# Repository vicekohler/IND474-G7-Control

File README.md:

# Control G7 — gamepad USB con pantalla para juegos de PC

**IND474 Desarrollo de Productos Físicos · Universidad Adolfo Ibáñez · Grupo 7**
Fernando Guaita · Guillermo Hidalgo · Vicente Kohler · Eduardo Rojas

Control G7 es un gamepad USB que el PC reconoce sin drivers. Tiene cruceta, A, B, MENU, un joystick analógico y una pantalla de 1,3" que muestra el modo y las confirmaciones. Funciona como **gamepad HID** (juegos de PC en general) o como **teclado** (juegos que solo aceptan teclado).

## Estado (23/11/2026)

| Parte | Estado |
|---|---|
| PCB D4.4 fabricada y soldada | ✅ |
| Firmware v1.2 (gamepad + teclado, pantalla, recalibración) | ✅ probado en gamepad-tester, SuperTux y el dinosaurio de Chrome |
| Carcasa v6 (Fusion 360) | ✅ diseñada · ⏳ sin imprimir |
| Bring-up medido (3V3, 5V, consumo) | ⏳ pendiente — ver [hardware/bring-up](hardware/bring-up/README.md) |
| Probeta de holguras y muestras CMF | ⏳ pendiente |
| Prueba con 5 usuarios | ⏳ pendiente — ver [experiencia](experiencia/README.md) |

Lo pendiente se marca así a propósito: no publicamos resultados que todavía no medimos.

## Cómo usarlo

1. Enchufar por USB-C **con el stick suelto** (se calibra el centro al conectar).
2. Windows lo muestra como **"Control G7"**.
3. Atajos:
   - **MENU + B (1,5 s):** cambia entre GAMEPAD y TECLADO (queda guardado).
   - **MENU + A (1,5 s):** recalibra el centro del stick.

| Control | Modo GAMEPAD | Modo TECLADO |
|---|---|---|
| Stick | Ejes X / Y | Flechas |
| Cruceta | Hat (con diagonales) | Flechas |
| A / B | Botón 1 / 2 | Z / X |
| MENU | Botón 8 (Start) | Enter |
| Clic del stick | Botón 9 (L3) | Espacio |

## Estructura del repositorio

| Carpeta | Contenido |
|---|---|
| [`hardware/`](hardware) | KiCad, Gerber, BOM, planos, DRC/ERC, cambios desde la D4.4 y bring-up |
| [`firmware/`](firmware) | Firmware `G7_Gamepad` v1.2 y las 4 pruebas por partes con sus lecturas |
| [`cad/`](cad) | Fusion 360 (`.f3d`), STEP del ensamble, STL para imprimir, renders, scripts y modelos de componentes |
| [`experiencia/`](experiencia) | Perfil de usuario, protocolo de la prueba con 5 personas, planilla y resultados |
| [`docs/`](docs) | Presentación (PDF), resumen de la carcasa y diagramas |
| [`DECISIONES.md`](DECISIONES.md) | Decisiones de diseño y por qué cambiaron desde la propuesta |

## Arquitectura

```
Cruceta, A, B, MENU ──┐
Joystick KY-023 ──────┼──► Waveshare RP2350-Plus ──► USB-C ──► PC (gamepad HID o teclado)
                      │     núcleo 0: entradas + USB a 1 kHz
                      │     núcleo 1: pantalla ST7789
```

- **Microcontrolador:** Waveshare RP2350-Plus, soldado por la cara trasera de la PCB.
- **Firmware:** Arduino-Pico 6.3.2 (Arduino IDE 2.3.11) + librerías Adafruit ST7789 y GFX.
- **Carcasa:** concha impresa en PLA/PETG (Bambu A1), pared de 2,4 mm; la PCB se atornilla a la tapa con 4 × M2 y la base cierra con 6 clips.

## Referencias

- [Alpakka — Input Labs](https://inputlabs.io/alpakka): referente de mando abierto (integración física y documentación).
- [Arduino-Pico](https://github.com/earlephilhower/arduino-pico): núcleo sobre el que corre el firmware.
- [Adafruit ST7735/ST7789](https://github.com/adafruit/Adafruit-ST7735-Library) y [Adafruit GFX](https://github.com/adafruit/Adafruit-GFX-Library).
- [Waveshare RP2350-Plus](https://www.waveshare.com/wiki/RP2350-Plus).
- Norman, Rams, Ulrich y Thompson (material del curso) para ergonomía, forma y CMF.

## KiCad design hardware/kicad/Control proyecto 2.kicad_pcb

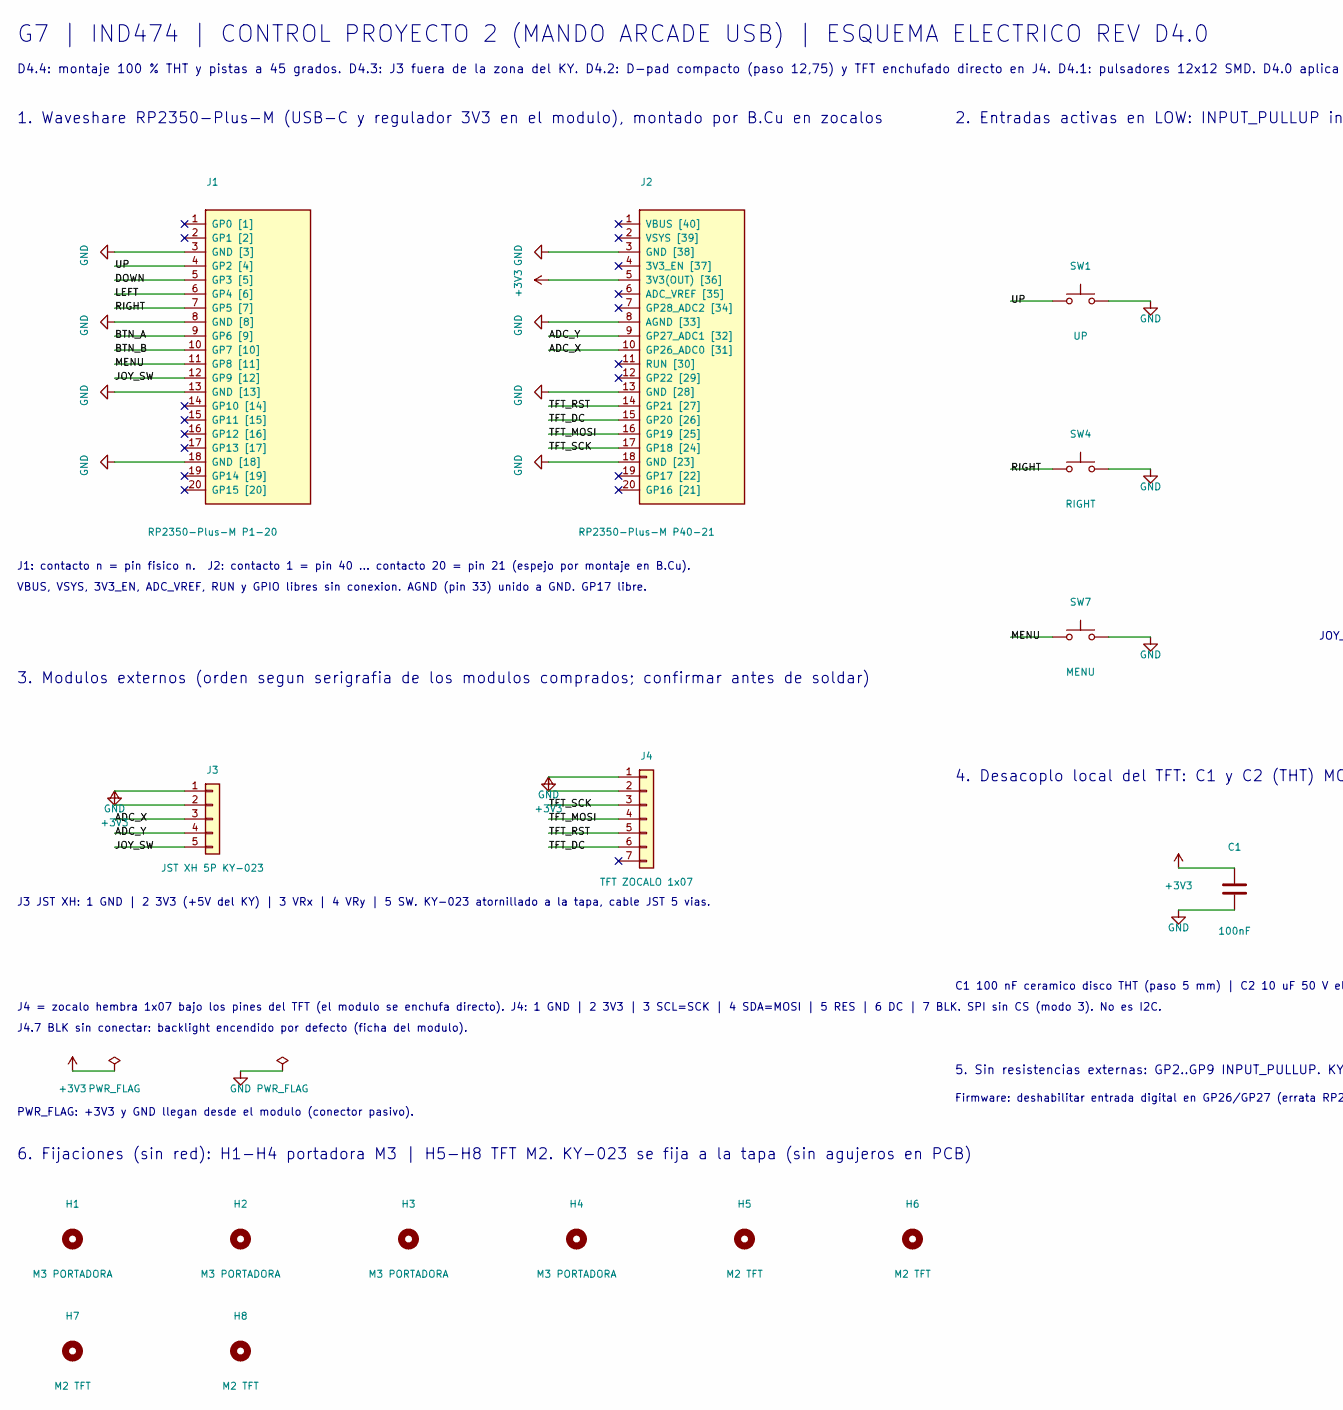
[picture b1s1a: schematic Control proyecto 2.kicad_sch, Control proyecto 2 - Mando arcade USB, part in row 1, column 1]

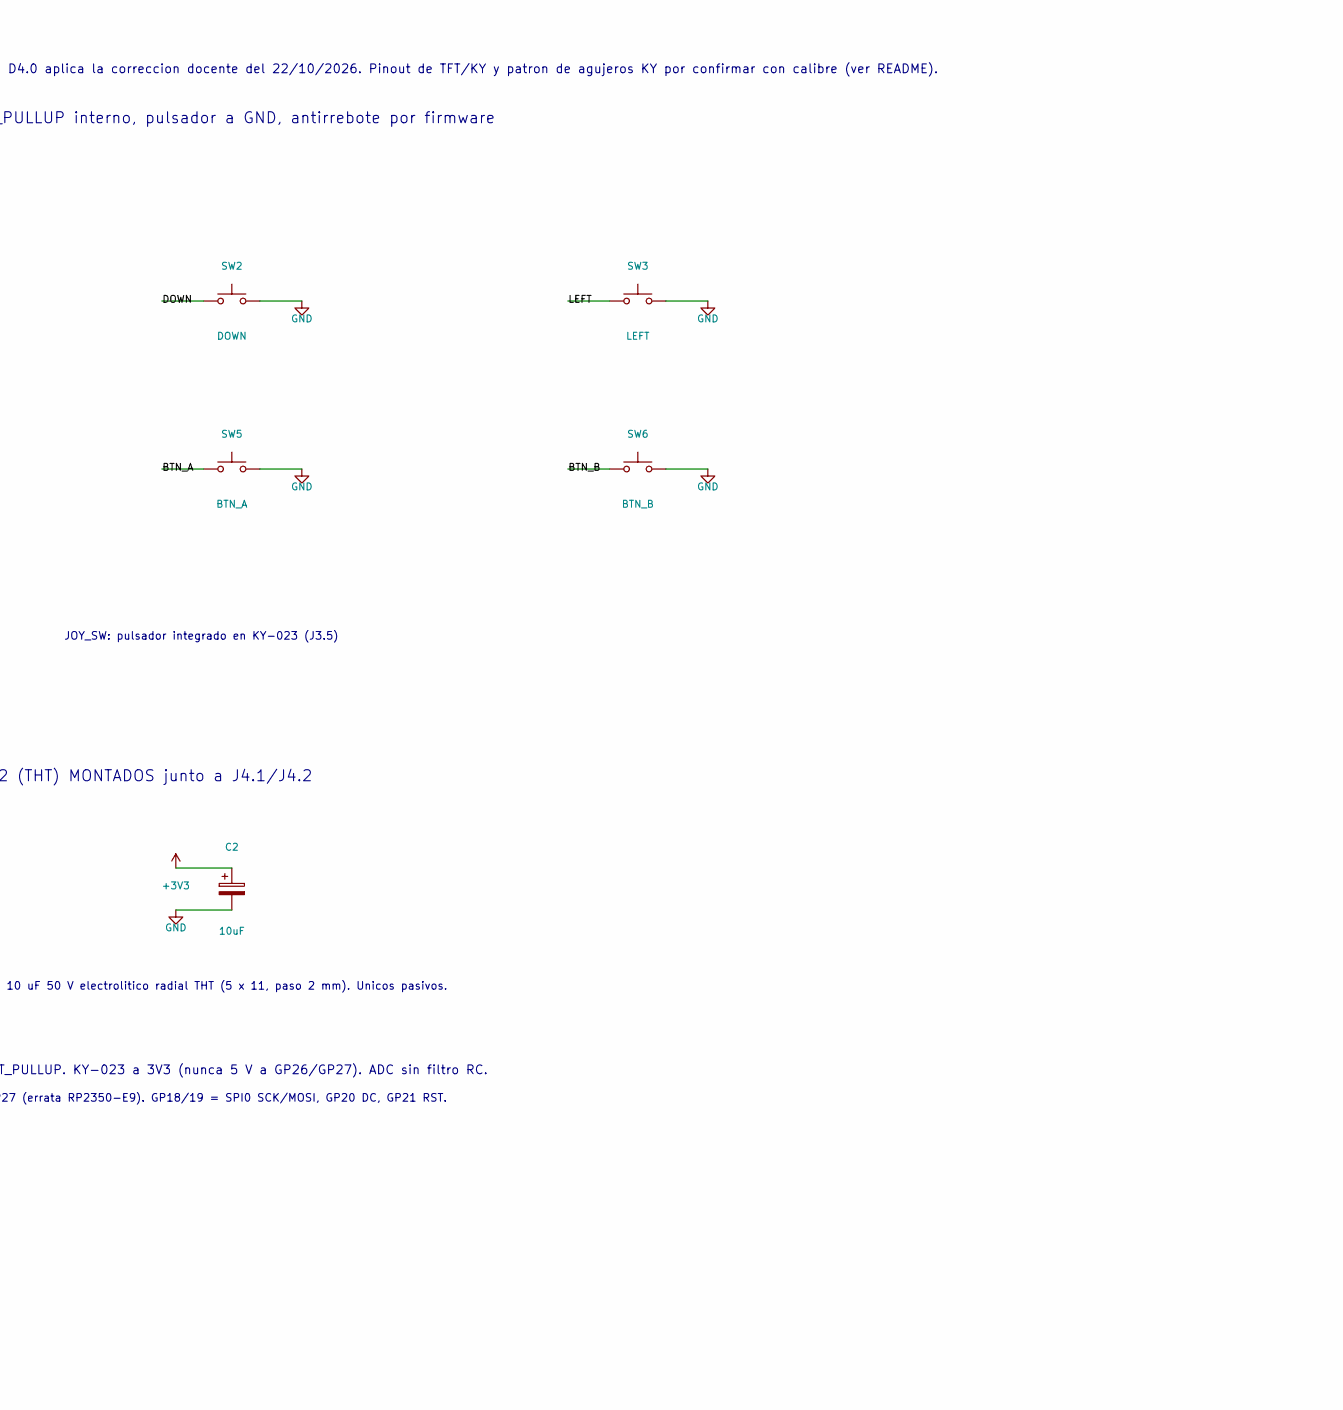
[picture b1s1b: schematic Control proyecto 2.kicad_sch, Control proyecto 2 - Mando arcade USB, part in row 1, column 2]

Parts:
C1: 100nF; C_Disc_D5.0mm_W2.5mm_P5.00mm; MPN K104K15X7RF5TL2
C2: 10uF; CP_Radial_D5.0mm_P2.00mm; MPN UVR1H100MDD
H1, H2, H3, H4: M3 PORTADORA; MountingHole_3.2mm_M3
H5, H6, H7, H8: M2 TFT; MountingHole_2.2mm_M2_TFT
J1: RP2350-Plus-M P1-20; PinSocket_1x20_P2.54mm_Vertical
J2: RP2350-Plus-M P40-21; PinSocket_1x20_P2.54mm_Vertical
J3: JST XH 5P KY-023; JST_XH_B5B-XH-A_1x05_P2.50mm_Vertical; MPN B5B-XH-A
J4: TFT ZOCALO 1x07; PinSocket_1x07_P2.54mm_Vertical
SW1: UP; SW_PUSH-12mm
SW2: DOWN; SW_PUSH-12mm
SW3: LEFT; SW_PUSH-12mm
SW4: RIGHT; SW_PUSH-12mm
SW5: BTN_A; SW_PUSH-12mm
SW6: BTN_B; SW_PUSH-12mm
SW7: MENU; SW_PUSH_6mm

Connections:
+3V3: C1.1, C2.1, J2.5 (3V3(OUT) [36]), J3.2, J4.2
/ADC_X: J2.10 (GP26_ADC0 [31]), J3.3
/ADC_Y: J2.9 (GP27_ADC1 [32]), J3.4
/BTN_A: J1.9 (GP6 [9]), SW5.1
/BTN_B: J1.10 (GP7 [10]), SW6.1
/DOWN: J1.5 (GP3 [5]), SW2.1
/JOY_SW: J1.12 (GP9 [12]), J3.5
/LEFT: J1.6 (GP4 [6]), SW3.1
/MENU: J1.11 (GP8 [11]), SW7.1
/RIGHT: J1.7 (GP5 [7]), SW4.1
/TFT_DC: J2.15 (GP20 [26]), J4.6
/TFT_MOSI: J2.16 (GP19 [25]), J4.4
/TFT_RST: J2.14 (GP21 [27]), J4.5
/TFT_SCK: J2.17 (GP18 [24]), J4.3
/UP: J1.4 (GP2 [4]), SW1.1
GND: C1.2, C2.2, J1.3 (GND [3]), J1.8 (GND [8]), J1.13 (GND [13]), J1.18 (GND [18]), J2.3 (GND [38]), J2.8 (AGND [33]), J2.13 (GND [28]), J2.18 (GND [23]), J3.1, J4.1, SW1.2, SW2.2, SW3.2, SW4.2, SW5.2, SW6.2, SW7.2

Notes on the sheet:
G7 | IND474 | CONTROL PROYECTO 2 (MANDO ARCADE USB) | ESQUEMA ELECTRICO REV D4.0
D4.4: montaje 100 % THT y pistas a 45 grados. D4.3: J3 fuera de la zona del KY. D4.2: D-pad compacto (paso 12,75) y TFT enchufado directo en J4. D4.1: pulsadores 12x12 SMD. D4.0 aplica la correccion docente del 22/10/2026. Pinout de TFT/KY y patron de agujeros KY por confirmar con calibre (ver READ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
1. Waveshare RP2350-Plus-M (USB-C y regulador 3V3 en el modulo), montado por B.Cu en zocalos
J1: contacto n = pin fisico n. J2: contacto 1 = pin 40 ... contacto 20 = pin 21 (espejo por montaje en B.Cu).
VBUS, VSYS, 3V3_EN, ADC_VREF, RUN y GPIO libres sin conexion. AGND (pin 33) unido a GND. GP17 libre.
2. Entradas activas en LOW: INPUT_PULLUP interno, pulsador a GND, antirrebote por firmware
JOY_SW: pulsador integrado en KY-023 (J3.5)
3. Modulos externos (orden segun serigrafia de los modulos comprados; confirmar antes de soldar)
PWR_FLAG: +3V3 y GND llegan desde el modulo (conector pasivo).
J3 JST XH: 1 GND | 2 3V3 (+5V del KY) | 3 VRx | 4 VRy | 5 SW. KY-023 atornillado a la tapa, cable JST 5 vias.
J4 = zocalo hembra 1x07 bajo los pines del TFT (el modulo se enchufa directo). J4: 1 GND | 2 3V3 | 3 SCL=SCK | 4 SDA=MOSI | 5 RES | 6 DC | 7 BLK. SPI sin CS (modo 3). No es I2C.
J4.7 BLK sin conectar: backlight encendido por defecto (ficha del modulo).
4. Desacoplo local del TFT: C1 y C2 (THT) MONTADOS junto a J4.1/J4.2
C1 100 nF ceramico disco THT (paso 5 mm) | C2 10 uF 50 V electrolitico radial THT (5 x 11, paso 2 mm). Unicos pasivos.
5. Sin resistencias externas: GP2..GP9 INPUT_PULLUP. KY-023 a 3V3 (nunca 5 V a GP26/GP27). ADC sin filtro RC.
Firmware: deshabilitar entrada digital en GP26/GP27 (errata RP2350-E9). GP18/19 = SPI0 SCK/MOSI, GP20 DC, GP21 RST.
6. Fijaciones (sin red): H1-H4 portadora M3 | H5-H8 TFT M2. KY-023 se fija a la tapa (sin agujeros en PCB)

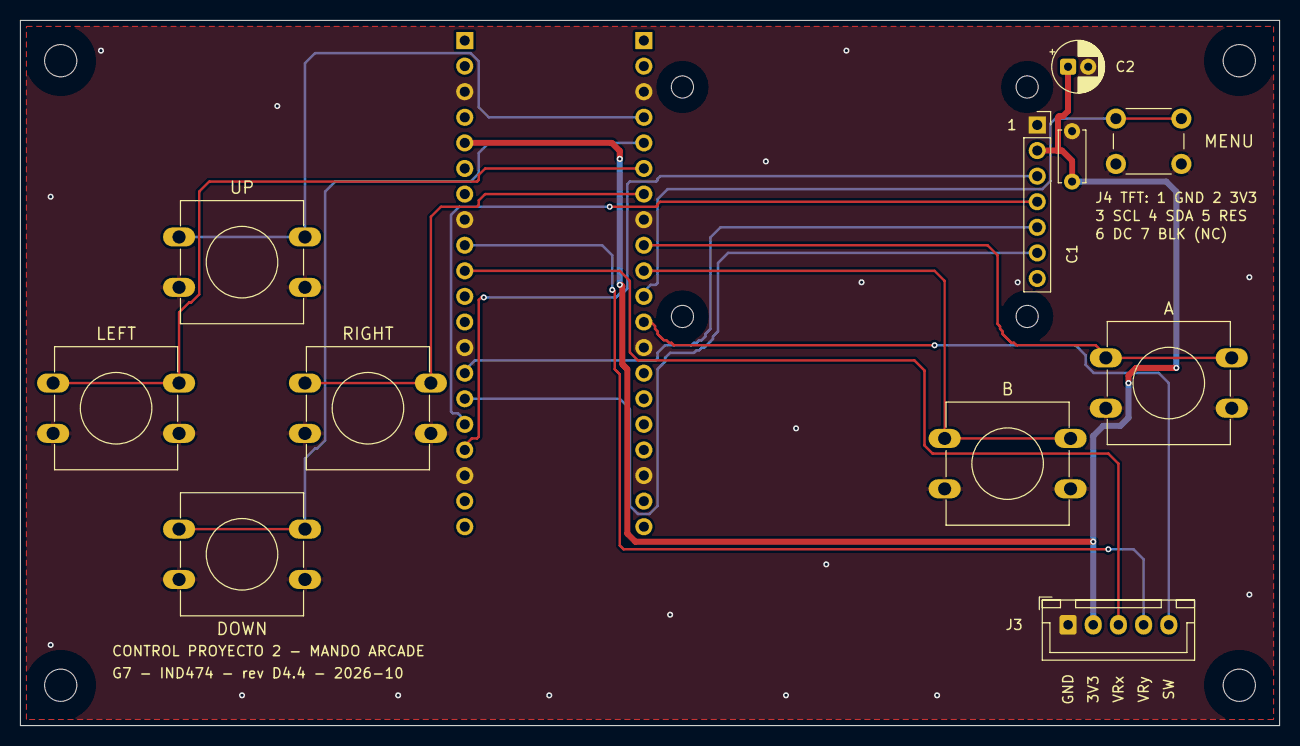
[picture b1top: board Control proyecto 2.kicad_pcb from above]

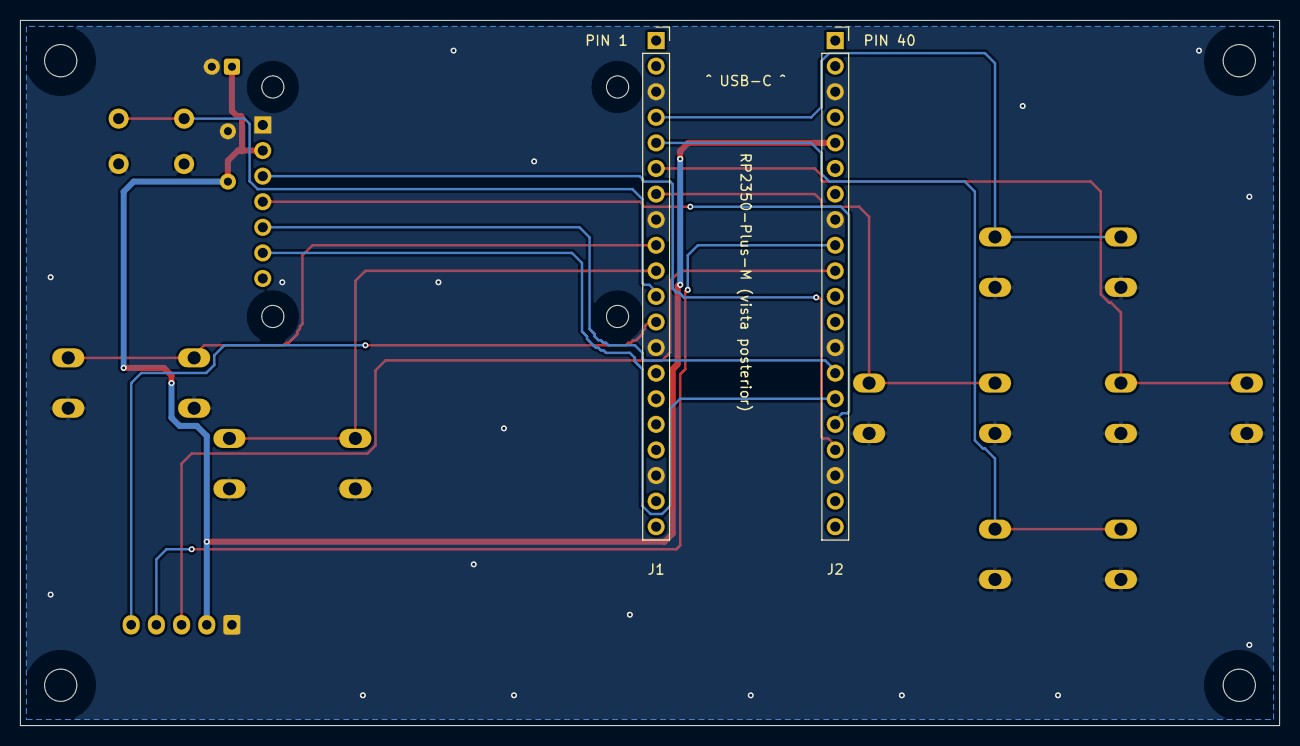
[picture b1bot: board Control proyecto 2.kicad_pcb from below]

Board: 2 copper layers, 125.0 x 70.0 mm, 21 parts (2 on the bottom side), 16 nets.

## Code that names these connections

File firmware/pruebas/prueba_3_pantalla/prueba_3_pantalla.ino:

// G7 - Control proyecto 2 - PRUEBA 3: PANTALLA TFT 1.3" ST7789 240x240 (7 pines, sin CS)
// Placa: Waveshare RP2350 Plus. Librerias: Adafruit ST7735 and ST7789 + Adafruit GFX.
// J4: 1 GND, 2 3V3, 3 SCL->GP18, 4 SDA->GP19, 5 RES->GP21, 6 DC->GP20, 7 BLK (sin conectar).
// Sin CS la pantalla necesita SPI modo 3.
// Secuencia: rojo, verde, azul, blanco; luego texto y una vista en vivo de botones y joystick.

#include <SPI.h>
#include <Adafruit_GFX.h>
#include <Adafruit_ST7789.h>

const int TFT_SCK = 18, TFT_MOSI = 19, TFT_DC = 20, TFT_RST = 21, TFT_CS = -1;
Adafruit_ST7789 tft(&SPI, TFT_CS, TFT_DC, TFT_RST);

const uint8_t PINES[8]   = {2, 3, 4, 5, 6, 7, 8, 9};
const char*   NOMBRES[8] = {"UP", "DOWN", "LEFT", "RIGHT", "A", "B", "MENU", "JOY"};

void setup() {
  Serial.begin(115200);
  for (int i = 0; i < 8; i++) pinMode(PINES[i], INPUT_PULLUP);
  analogReadResolution(12);

  SPI.setSCK(TFT_SCK);
  SPI.setTX(TFT_MOSI);
  tft.init(240, 240, SPI_MODE3);
  tft.setRotation(1);   // contenido girado 90 grados para leerlo horizontal
  Serial.println("TFT iniciada");

  uint16_t colores[4] = {ST77XX_RED, ST77XX_GREEN, ST77XX_BLUE, ST77XX_WHITE};
  const char* nombres[4] = {"rojo", "verde", "azul", "blanco"};
  for (int i = 0; i < 4; i++) {
    tft.fillScreen(colores[i]);
    Serial.print("Pantalla en "); Serial.println(nombres[i]);
    delay(800);
  }
  tft.fillScreen(ST77XX_BLACK);
  tft.setTextColor(ST77XX_WHITE);
  tft.setTextSize(3);
  tft.setCursor(20, 10);  tft.print("G7 - D4.4");
  tft.setTextSize(2);
  tft.setCursor(20, 45);  tft.print("Pantalla OK");
}

void loop() {
  int x = analogRead(26), y = analogRead(27);
  Serial.printf("X=%d Y=%d\n", x, y);
  tft.setTextSize(2);
  tft.setTextColor(ST77XX_YELLOW, ST77XX_BLACK);
  tft.setCursor(10, 80);  tft.printf("X:%4d  Y:%4d ", x, y);
  for (int i = 0; i < 8; i++) {
    bool p = (digitalRead(PINES[i]) == LOW);
    tft.setCursor(10 + (i % 2) * 120, 110 + (i / 2) * 30);
    tft.setTextColor(p ? ST77XX_BLACK : ST77XX_WHITE, p ? ST77XX_GREEN : ST77XX_BLACK);
    tft.printf("%-6s", NOMBRES[i]);
  }
  delay(50);
}
